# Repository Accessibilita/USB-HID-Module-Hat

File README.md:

# USB-HID-Module-Hat
Raspberry Pi Hat that adds RS485 communication to Raspberry Pi 5 for interfacting with USB and Bluetooth HID Devices

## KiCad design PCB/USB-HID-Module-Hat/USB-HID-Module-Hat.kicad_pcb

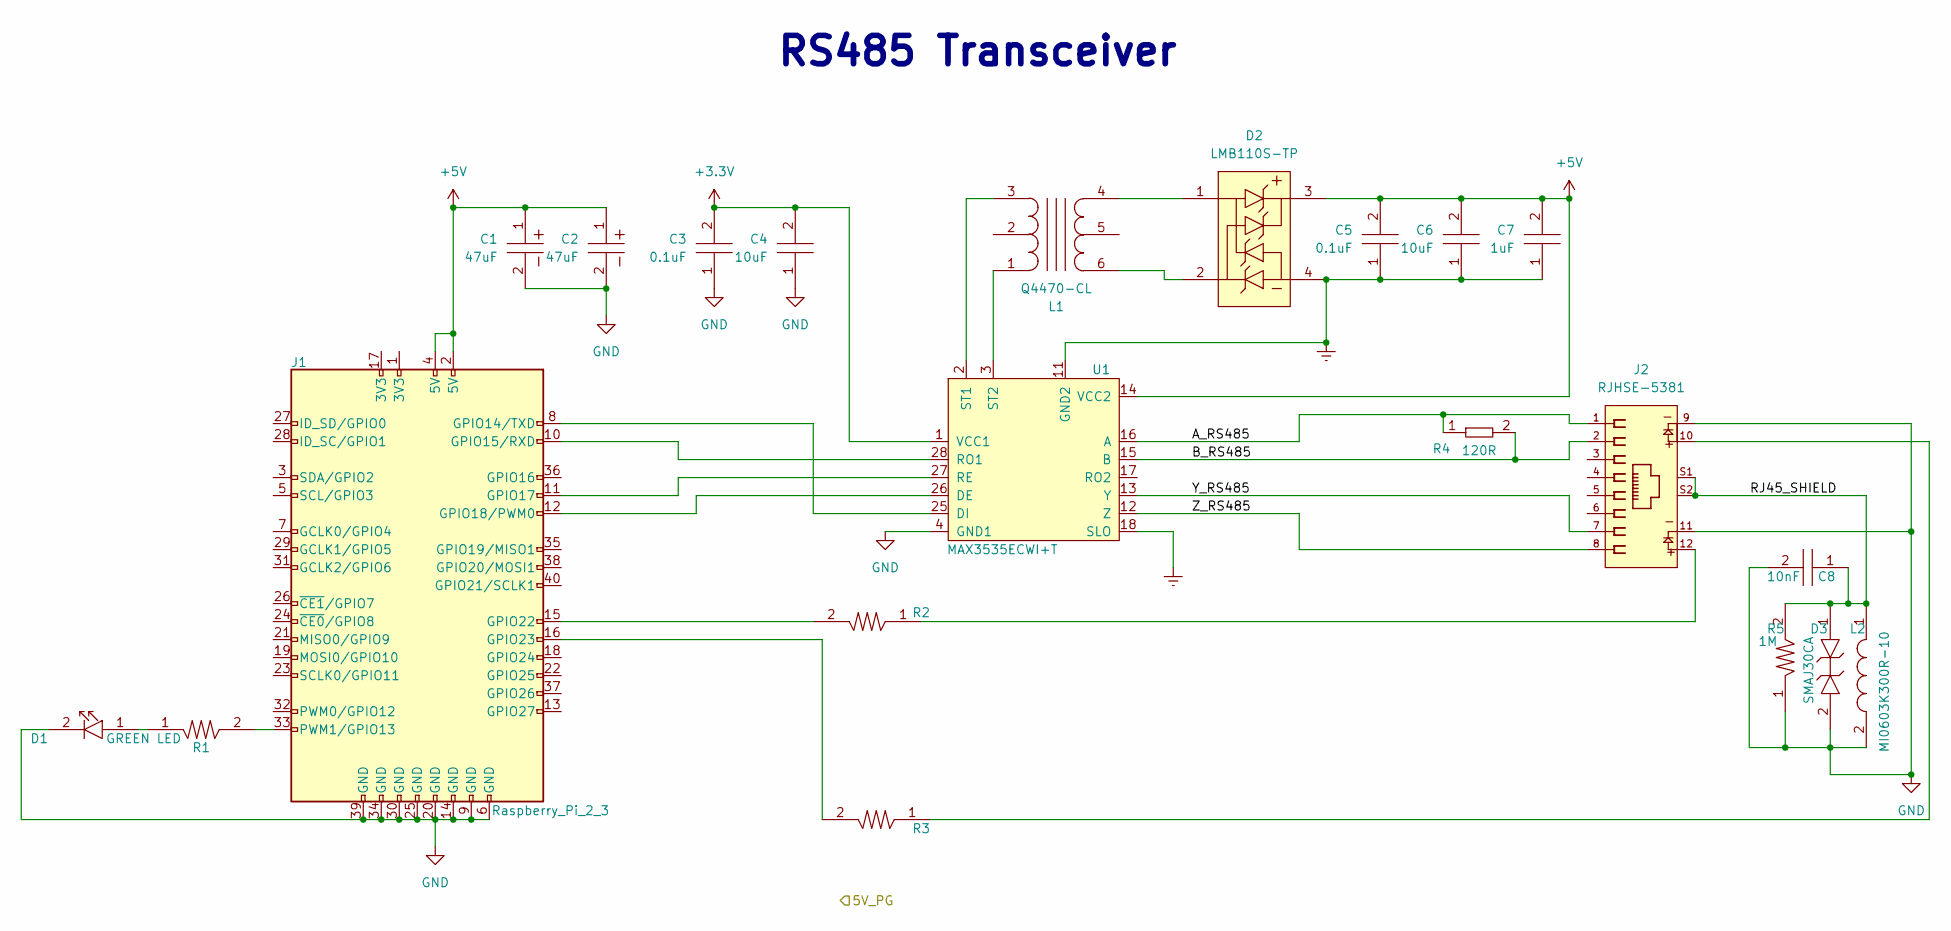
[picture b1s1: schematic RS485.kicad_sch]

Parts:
C1, C2: UCM1C470MCL1GS; Tolerance 20%; Voltage 16V; MFR# UCM1C470MCL1GS
C3, C5: CL10B104JB8NNNC; C0603; Tolerance 5%; Voltage 50V; MFR# CL10B104JB8NNNC
C4, C6: CGA5L3X5R1V106K160AB; C1206; Tolerance 10%; Voltage 35V; MFR# CGA5L3X5R1V106K160AB
C7: C1206C105K3RACAUTO; D_SOD-123; Tolerance 10%; Voltage 25V; MFR# C1206C105K3RACAUTO
C8: C0805C103KCRACAUTO; C0805; Tolerance 10%; Voltage 500V; MFR# C0805C103KCRACAUTO
D1: LTST-C194KGKT; LED0603; Tolerance *; Voltage 2.1V; MFR# LTST-C194KGKT
D2: LMB110S-TP; Tolerance *; Voltage 850 mV @ 500 mA; MFR# LMB110S-TP
D3: SMAJ30CA; Tolerance *; Voltage 30V Clamp; MFR# SMAJ30CA
J1: Raspberry_Pi_2_3; SULLINS_PPPC202LFBN-RC_RPi5
J2: RJHSE-5381; AMPHENOL_RJHSE-5381; Tolerance *; Voltage *; MFR# RJHSE-5381
L1: Q4470-CL; SO6_Q4470-CL_C-SIZE_COC; Tolerance *; Voltage 5V; MFR# Q4470-CL
L2: MI0603K300R-10; Tolerance *; Voltage *; MFR# MI0603K300R-10
R1, R2, R3: RC0603FR-07470RL; R0603; Tolerance 1%; Voltage *; MFR# RC0603FR-07470RL
R4: AC0402FR-07120RL; R0402; Tolerance 1%; Voltage *; MFR# AC0402FR-07120RL
R5: RC1206FR-071ML; R1206; Tolerance 1%; Voltage *; MFR# RC1206FR-071ML
U1: MAX3535ECWI+T; 21-0145_W28M&plus_9_MXM; Tolerance N/A; Voltage 3-5.5V; MFR# MAX3535ECWI+T

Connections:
+3.3V: C3.2, C4.2, U1.1 (VCC1); also elsewhere on the board
+5V: C1.1, C2.1, C5.2, C6.2, C7.2, D2.3, J1.2 (5V), J1.4 (5V), U1.14 (VCC2); also elsewhere on the board
/RS485/A_RS485: J2.1, R4.1, U1.16 (A)
/RS485/B_RS485: J2.2, R4.2, U1.15 (B)
/RS485/RJ45_SHIELD: C8.1, D3.1, J2.S1, J2.S2, L2.1, R5.2
/RS485/Y_RS485: J2.7, U1.13 (Y)
/RS485/Z_RS485: J2.8, U1.12 (Z)
Earth: C5.1, C6.1, C7.1, D2.4, U1.11 (GND2), U1.18 (SLO)
GND: C1.2, C2.2, C3.1, C4.1, C8.2, D1.2, D3.2, J1.6 (GND), J1.9 (GND), J1.14 (GND), J1.20 (GND), J1.25 (GND), J1.30 (GND), J1.34 (GND), J1.39 (GND), J2.9, J2.11, L2.2, R5.1, U1.4 (GND1); also elsewhere on the board
unnamed: D1.1, R1.1
unnamed: D2.1, L1.4
unnamed: D2.2, L1.6
unnamed: J1.8 (GPIO14/TXD), U1.25 (DI)
unnamed: J1.10 (GPIO15/RXD), U1.28 (RO1)
unnamed: J1.11 (GPIO17), U1.27 (RE)
unnamed: J1.12 (GPIO18/PWM0), U1.26 (DE)
unnamed: J1.15 (GPIO22), R2.2
unnamed: J1.16 (GPIO23), R3.2
unnamed: J1.33 (PWM1/GPIO13), R1.2
unnamed: J2.10, R3.1
unnamed: J2.12, R2.1
unnamed: L1.3, U1.2 (ST1)
unnamed: L1.1, U1.3 (ST2)

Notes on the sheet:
RS485 Transceiver

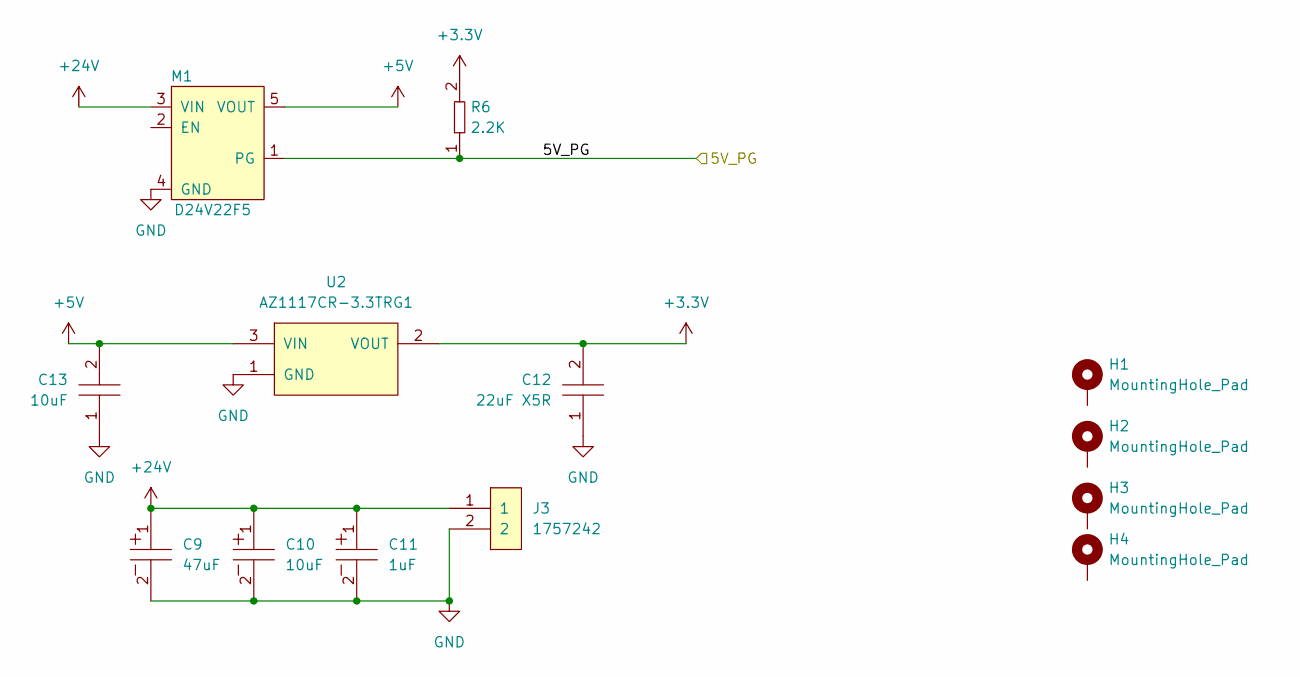
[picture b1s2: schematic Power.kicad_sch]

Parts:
C9: UUQ1H470MCL1GS; CP_Elec_8x10; Tolerance 20%; Voltage 50V; MFR# UUQ1H470MCL1GS
C10: UUQ1H100MCL1GB; CAP_UUQ_6P3X5P4_NCH; Tolerance 20%; Voltage 50V; MFR# UUQ1H100MCL1GB
C11: UUQ1H010MCL1GB; CAP_UUQ_4X5P4_NCH; Tolerance 20%; Voltage 50V; MFR# UUQ1H010MCL1GB
C12: GRM21BR61A226ME51L; C0805; Tolerance 20%; Voltage 10V; MFR# GRM21BR61A226ME51L
C13: GRT31CR61H106KE01L; C1206; Tolerance 10%; Voltage 50V; MFR# GRT31CR61H106KE01L
H1, H2, H3, H4: MountingHole_Pad; RPI_HAT_HOLE
J3: 1757242; PhoenixContact_MSTBA-G_02x5.08mm_Angled; Tolerance *; Voltage 300V; MFR# 1757242
M1: D24V22F5; D24V22F12; Tolerance N/A; Voltage 36V IN 5V OUT; MFR# D24V22F5
R6: RC0603FR-072K2L; R0603; Tolerance 1%; Voltage N/A; MFR# RC0603FR-072K2L
U2: AZ1117CR-3.3TRG1; SOT_89; Tolerance *; Voltage 15IN, 3V3 OUT; MFR# AZ1117CR-3.3TRG1

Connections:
+3.3V: C12.2, R6.2, U2.2 (VOUT); also elsewhere on the board
+5V: C13.2, M1.5 (VOUT), U2.3 (VIN); also elsewhere on the board
+24V: C9.1, C10.1, C11.1, J3.1, M1.3 (VIN)
/Power/5V_PG: M1.1 (PG), R6.1
GND: C9.2, C10.2, C11.2, C12.1, C13.1, J3.2, M1.4 (GND), U2.1 (GND); also elsewhere on the board

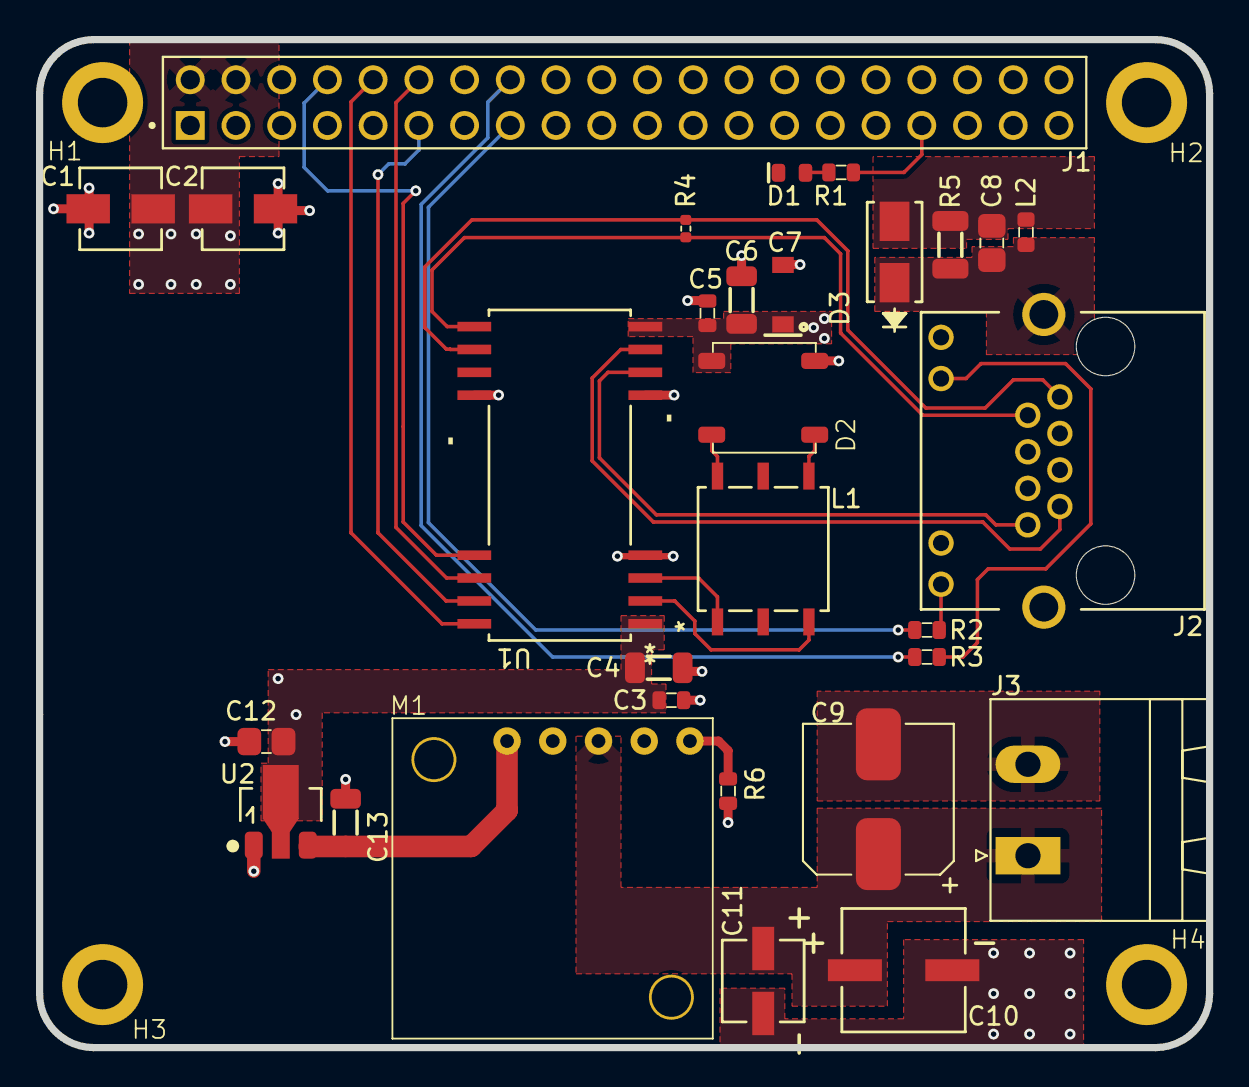
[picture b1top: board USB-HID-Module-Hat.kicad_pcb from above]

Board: 4 copper layers, 65.0 x 56.0 mm, 34 parts (0 on the bottom side), 25 nets.

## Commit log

2024-08-27 Schematic Capture
    Schematic capture complete !
2024-08-27 Create License.md
    Added license
2024-08-27 Revised Scheamtic
    Added schematic pages and added power schematic
2024-08-27 PCB
    PCB layout 80% complete. Board shape defined. Components and connectors places !
2024-09-03 First Pass at PCB
    PCB layout completed, pending design review.
2025-03-11 Gitignore
    gitignore updated

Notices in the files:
parts and their libraries:
Copyright 2016 Accelerated Designs. All rights reserved.
